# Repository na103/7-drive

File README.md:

# 7-drive
7-drive is a remake of an Amiga accessory made by the company Logica in Italy, it is installed on the external drive port and can show, in the 7-segment display, the activity of the df0 or df1 drive.
<br>
it's not particularly useful, maybe it was in the past when you spent your time copying hundreds of floppies.<br>
however it seems nice to me as an object to add to our amiga.
<br><br>

<br>
you can see 7-drive in action in this [short video](https://youtu.be/NdRC49Pznj0)
<br><br>

## Bill of materials
| Qt. |    Description     |             Designator          |    Mouser  Part    |             Note              |
|:---:|--------------------|---------------------------------|--------------------|-------------------------------|
|1    |74LS27              | U2                              |SN74LS27N           |                               |
|1    |74LS00              | U3                              |SN74LS00N           |                               |
|2    |Decade up-down counter| U4 U5                         |CD40110BE           |                               |
|2    |7 segment display   | DS1 DS2                         |TDSO3160-L          |                               |
|2    |Diode 1N4148        | D1 D2                           |1N4148              |                               |
|1    |Resistor 3.9K       | R1                              |MFR25SFTE26-3K9     |                               |
|4    |Resistor net. 220R  | RN1 - RN4                       |4608X-102-221LF     |                               |
|1    |Capacitor 4.7 nF    | C1                              |K472J20C0GF5TH5     |                               |
|2    |Capacitor 100 nF    | C2 C3                           |K104K15X7RF5TH5     |                               |
|1    |Switch 2P3T         | SW1                             |EG1201A             |                               |
|1    |Db23 male           | J1                              |                    |    on ebay or [amigatore.eu](https://amigastore.eu/en/790-db23-male-connector.html)    |
|1    |Db23 female         | J2                              |                    |    on ebay or [amigastore.eu](https://amigastore.eu/en/810-db23-female-connector.html)   |
|1    |15-Pin female header| J3                              |15Fx1-254mm         |                               |
|1    |18-Pin male header  | J5                              |22-28-4183          |                               |
|1    |15-Pin male header  | J6                              |22-28-8152          |                               |

here you can find the mouser project with all the components, Db23 connectors excluded.
[https://www.mouser.com/ProjectManager/ProjectDetail.aspx?AccessID=75b1d9bf4b](https://www.mouser.com/ProjectManager/ProjectDetail.aspx?AccessID=75b1d9bf4b)

## Building notes

* you can see [here](https://github.com/na103/7-drive/tree/main/img) the steps to follow to build the board.
* gerber of the three board is inside kicad projects
* switch in upper position show DF0 activity, down DF1
* is avaible an optional 3d printed case. thanks to Roberto Camparini for stl file

<br>
If you found this my work useful, please consider buying me a cup of coffee if you want:<br>

# License

This work is licensed under a Creative Commons Attribution 4.0 International License. See [https://creativecommons.org/licenses/by/4.0/](https://creativecommons.org/licenses/by/4.0/).

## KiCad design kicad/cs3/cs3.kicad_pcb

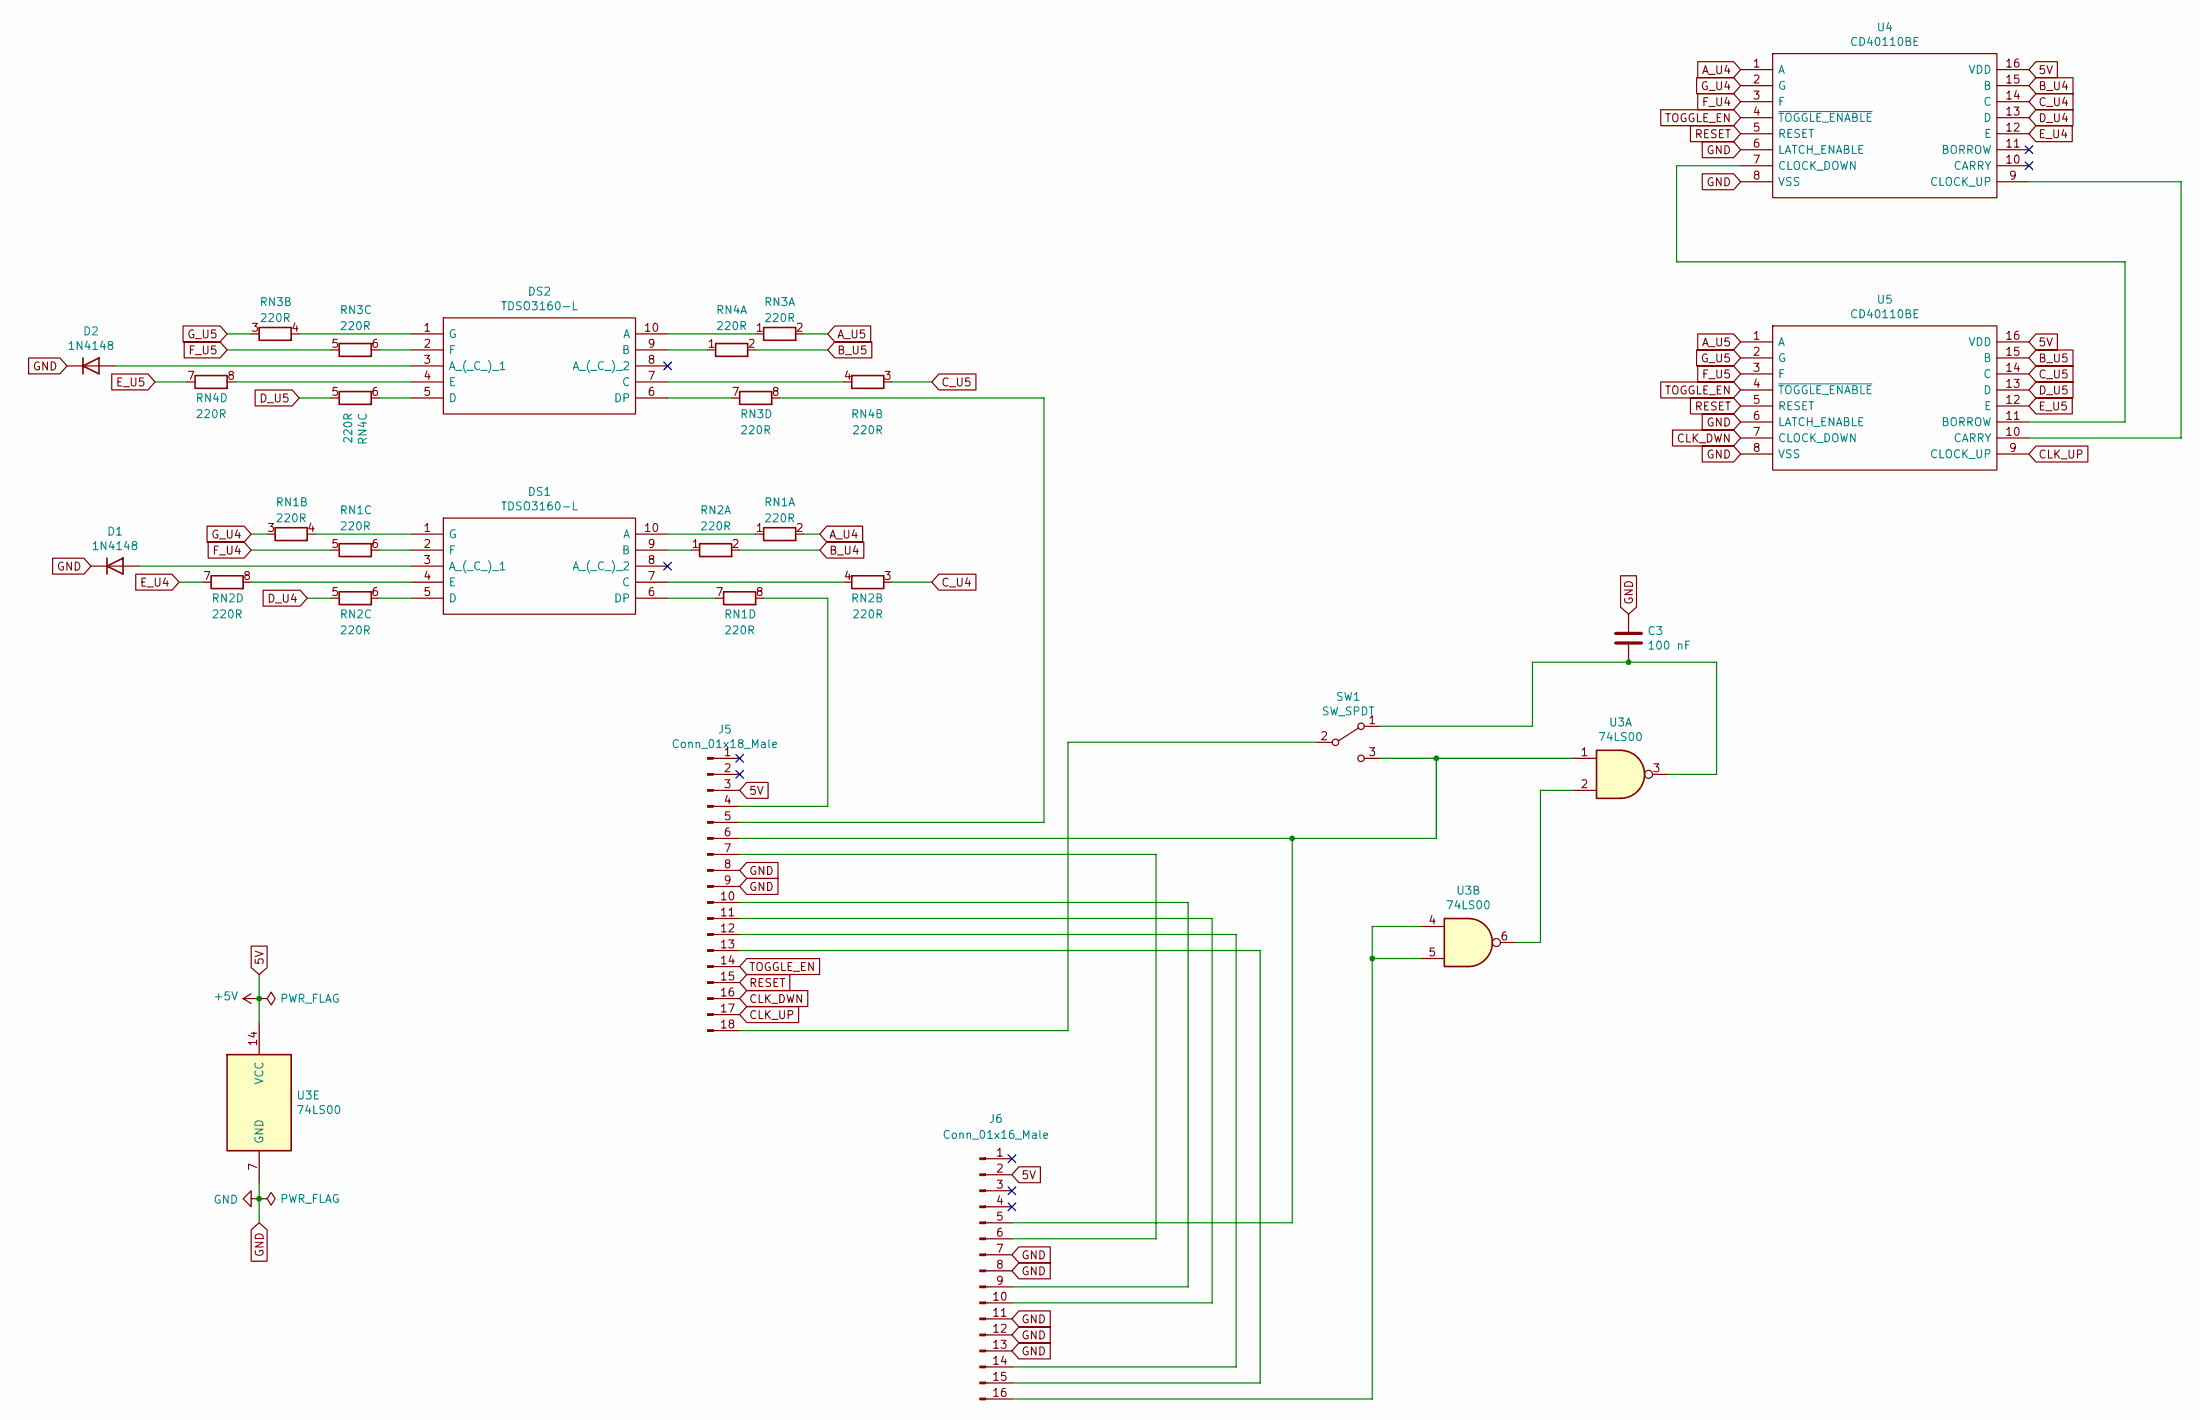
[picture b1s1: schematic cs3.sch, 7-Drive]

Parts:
C3: 100 nF; C_Disc_D6.0mm_W2.5mm_P5.00mm
D1, D2: 1N4148; D_A-405_P7.62mm_Horizontal
DS1, DS2: TDSO3160-L; TDSO3160L; Manufacturer_Part_Number TDSO3160-L; Mouser Part Number 78-TDSO3160-L
J5: Conn_01x18_Male; PinHeader_1x18_P2.54mm_Vertical
J6: Conn_01x16_Male; PinHeader_1x16_P2.54mm_Horizontal
RN1, RN2, RN3, RN4: 220R; R_Array_SIP8
SW1: SW_SPDT; SW_Slide_1P2T_SPDT
U3: 74LS00; DIP-14_W7.62mm
U4, U5: CD40110BE; DIP794W53P254L1930H508Q16N; Manufacturer_Part_Number CD40110BE; Mouser Part Number 595-CD40110BE

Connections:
5V: J5.3, J6.2, U3.14 (VCC), U4.16 (VDD), U5.16 (VDD)
A_U4: RN1.2 (R1.2), U4.1 (A)
A_U5: RN3.2 (R1.2), U5.1 (A)
B_U4: RN2.2 (R1.2), U4.15 (B)
B_U5: RN4.2 (R1.2), U5.15 (B)
CLK_DWN: J5.16, U5.7 (CLOCK_DOWN)
CLK_UP: J5.17, U5.9 (CLOCK_UP)
C_U4: RN2.3 (R2.1), U4.14 (C)
C_U5: RN4.3 (R2.1), U5.14 (C)
D_U4: RN2.5 (R3.1), U4.13 (D)
D_U5: RN4.5 (R3.1), U5.13 (D)
E_U4: RN2.7 (R4.1), U4.12 (E)
E_U5: RN4.7 (R4.1), U5.12 (E)
F_U4: RN1.5 (R3.1), U4.3 (F)
F_U5: RN3.5 (R3.1), U5.3 (F)
GND: C3.1, D1.1 (K), D2.1 (K), J5.8, J5.9, J6.7, J6.8, J6.11, J6.12, J6.13, U3.7 (GND), U4.6 (LATCH_ENABLE), U4.8 (VSS), U5.6 (LATCH_ENABLE), U5.8 (VSS)
G_U4: RN1.3 (R2.1), U4.2 (G)
G_U5: RN3.3 (R2.1), U5.2 (G)
unnamed: C3.2, SW1.1 (A), U3.3
unnamed: D1.2 (A), DS1.3 (A_(_C_)_1)
unnamed: D2.2 (A), DS2.3 (A_(_C_)_1)
unnamed: DS1.1 (G), RN1.4 (R2.2)
unnamed: DS1.2 (F), RN1.6 (R3.2)
unnamed: DS1.4 (E), RN2.8 (R4.2)
unnamed: DS1.5 (D), RN2.6 (R3.2)
unnamed: DS1.6 (DP), RN1.7 (R4.1)
unnamed: DS1.7 (C), RN2.4 (R2.2)
unnamed: DS1.9 (B), RN2.1 (R1.1)
unnamed: DS1.10 (A), RN1.1 (R1.1)
unnamed: DS2.1 (G), RN3.4 (R2.2)
unnamed: DS2.2 (F), RN3.6 (R3.2)
unnamed: DS2.4 (E), RN4.8 (R4.2)
unnamed: DS2.5 (D), RN4.6 (R3.2)
unnamed: DS2.6 (DP), RN3.7 (R4.1)
unnamed: DS2.7 (C), RN4.4 (R2.2)
unnamed: DS2.9 (B), RN4.1 (R1.1)
unnamed: DS2.10 (A), RN3.1 (R1.1)
unnamed: J5.4, RN1.8 (R4.2)
unnamed: J5.5, RN3.8 (R4.2)
unnamed: J5.6, J6.5, SW1.3 (C), U3.1
unnamed: J5.7, J6.6
unnamed: J5.10, J6.9
unnamed: J5.11, J6.10
unnamed: J5.12, J6.14
unnamed: J5.13, J6.15
unnamed: J5.18, SW1.2 (B)
unnamed: J6.16, U3.4, U3.5
unnamed: U3.2, U3.6
unnamed: U4.7 (CLOCK_DOWN), U5.11 (BORROW)
unnamed: U4.9 (CLOCK_UP), U5.10 (CARRY)
RESET: J5.15, U4.5 (RESET), U5.5 (RESET)
TOGGLE_EN: J5.14, U4.4 (~TOGGLE_ENABLE), U5.4 (~TOGGLE_ENABLE)

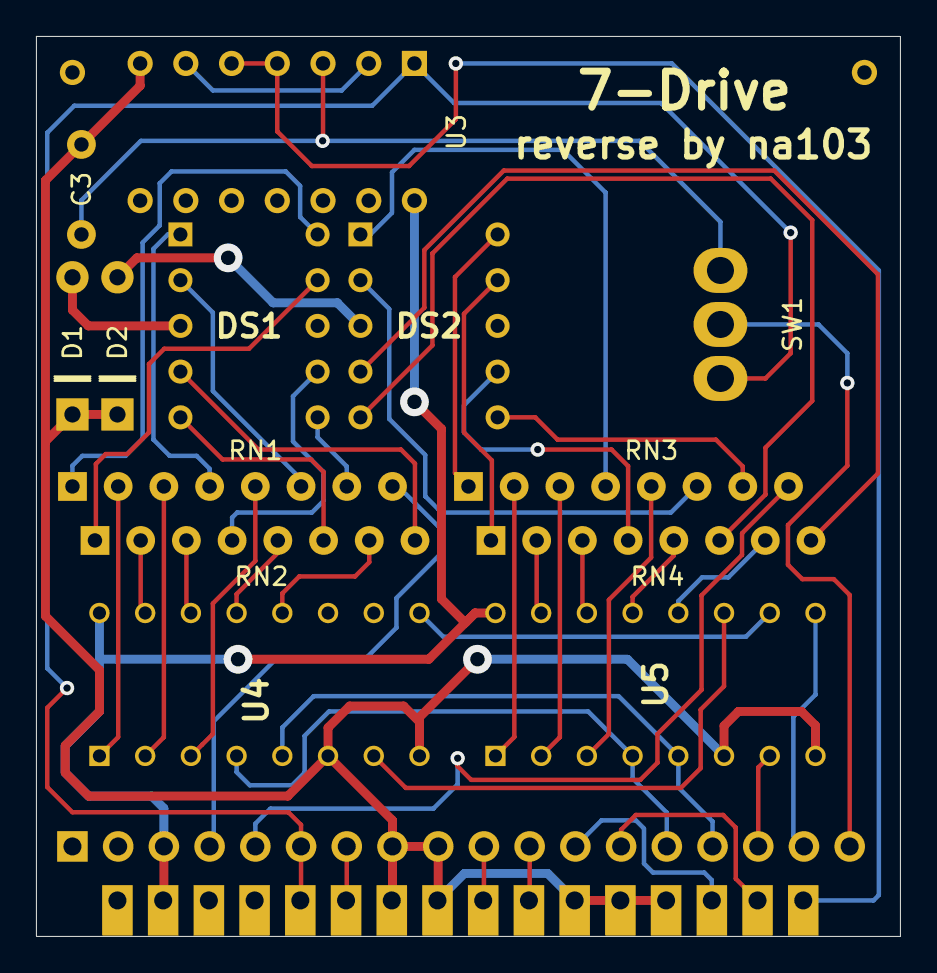
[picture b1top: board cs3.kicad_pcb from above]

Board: 2 copper layers, 48.0 x 50.0 mm, 15 parts (1 on the bottom side), 52 nets.

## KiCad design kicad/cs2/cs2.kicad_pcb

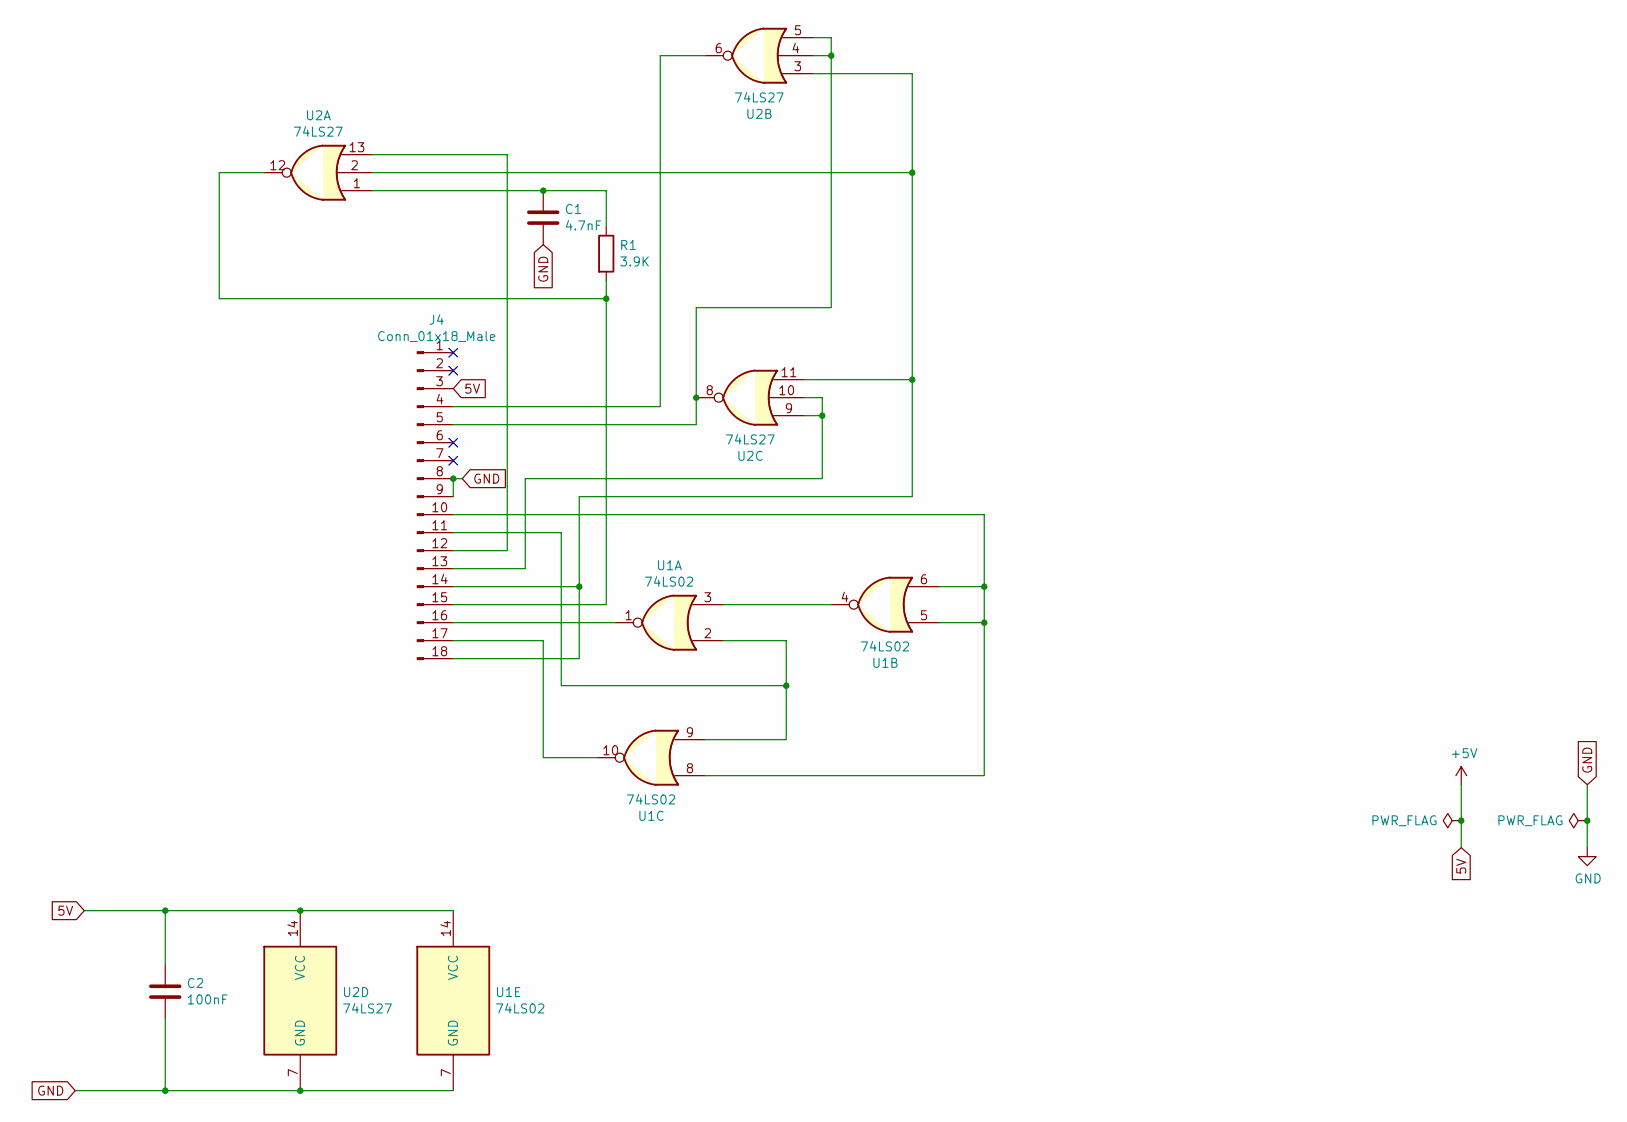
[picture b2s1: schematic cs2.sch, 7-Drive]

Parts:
C1: 4.7nF; C_Disc_D4.3mm_W1.9mm_P5.00mm
C2: 100nF; C_Disc_D4.3mm_W1.9mm_P5.00mm
J4: Conn_01x18_Male; PinHeader_1x18_P2.54mm_Vertical
R1: 3.9K; R_Axial_DIN0207_L6.3mm_D2.5mm_P10.16mm_Horizontal
U1: 74LS02; DIP-14_W7.62mm
U2: 74LS27; DIP-14_W7.62mm

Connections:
5V: C2.1, J4.3, U1.14 (VCC), U2.14 (VCC)
GND: C1.2, C2.2, J4.8, J4.9, U1.7 (GND), U2.7 (GND)
unnamed: C1.1, R1.1, U2.1
unnamed: J4.4, U2.6
unnamed: J4.5, U2.4, U2.5, U2.8
unnamed: J4.10, U1.5, U1.6, U1.8
unnamed: J4.11, U1.2, U1.9
unnamed: J4.12, U2.13
unnamed: J4.13, U2.9, U2.10
unnamed: J4.14, J4.18, U2.2, U2.3, U2.11
unnamed: J4.15, R1.2, U2.12
unnamed: J4.16, U1.1
unnamed: J4.17, U1.10
unnamed: U1.3, U1.4

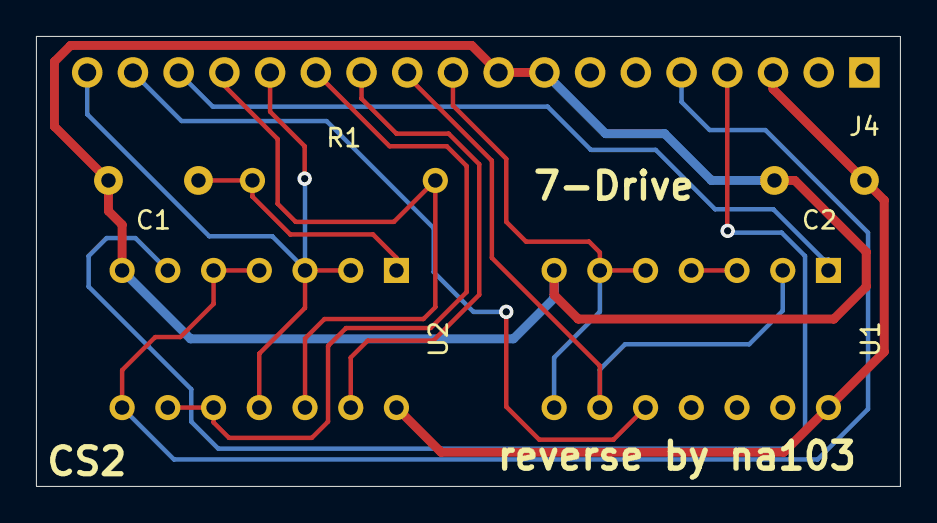
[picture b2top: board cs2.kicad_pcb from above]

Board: 2 copper layers, 48.0 x 25.0 mm, 6 parts (0 on the bottom side), 14 nets.

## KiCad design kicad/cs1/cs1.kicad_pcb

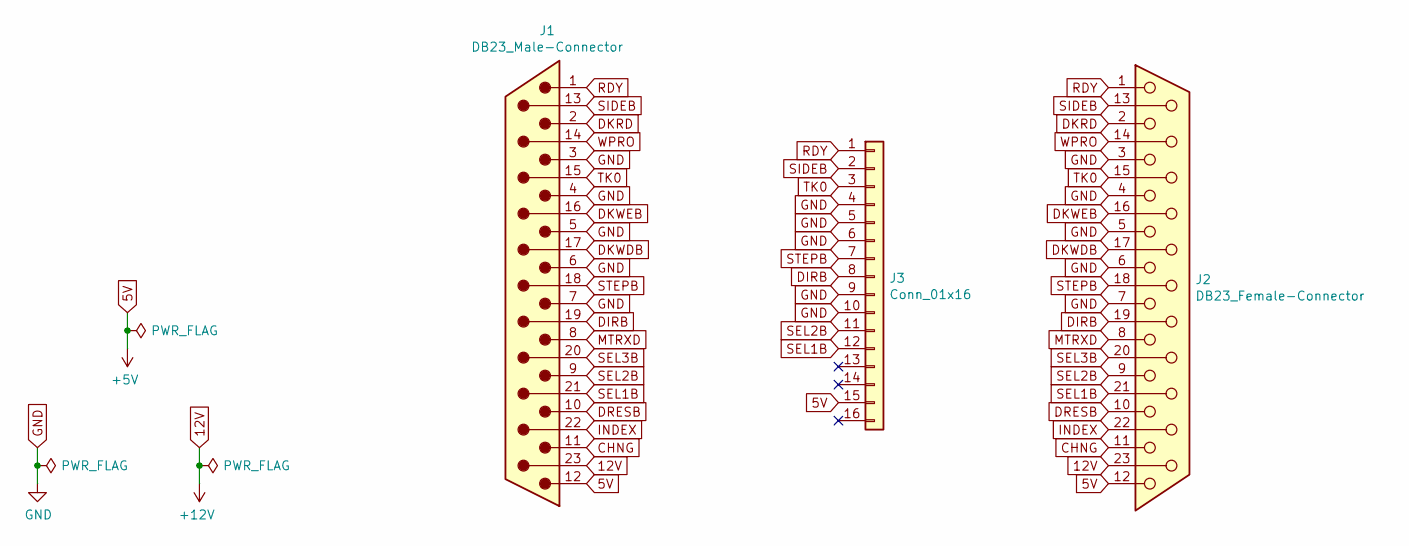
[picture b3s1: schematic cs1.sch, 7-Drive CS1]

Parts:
J1: DB23_Male-Connector; DSUB-23_Male_EdgeMount_P2.77mm
J2: DB23_Female-Connector; DSUB-23_Female_EdgeMount_P2.77mm
J3: Conn_01x16; PinHeader_1x16_P2.54mm_Vertical

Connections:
5V: J1.12, J2.12, J3.15
12V: J1.23, J2.23
CHNG: J1.11, J2.11
DIRB: J1.19, J2.19, J3.8
DKRD: J1.2, J2.2
DKWDB: J1.17, J2.17
DKWEB: J1.16, J2.16
DRESB: J1.10, J2.10
GND: J1.3, J1.4, J1.5, J1.6, J1.7, J2.3, J2.4, J2.5, J2.6, J2.7, J3.4, J3.5, J3.6, J3.9, J3.10
INDEX: J1.22, J2.22
MTRXD: J1.8, J2.8
RDY: J1.1, J2.1, J3.1
SEL1B: J1.21, J2.21, J3.12
SEL2B: J1.9, J2.9, J3.11
SEL3B: J1.20, J2.20
SIDEB: J1.13, J2.13, J3.2
STEPB: J1.18, J2.18, J3.7
TK0: J1.15, J2.15, J3.3
WPRO: J1.14, J2.14

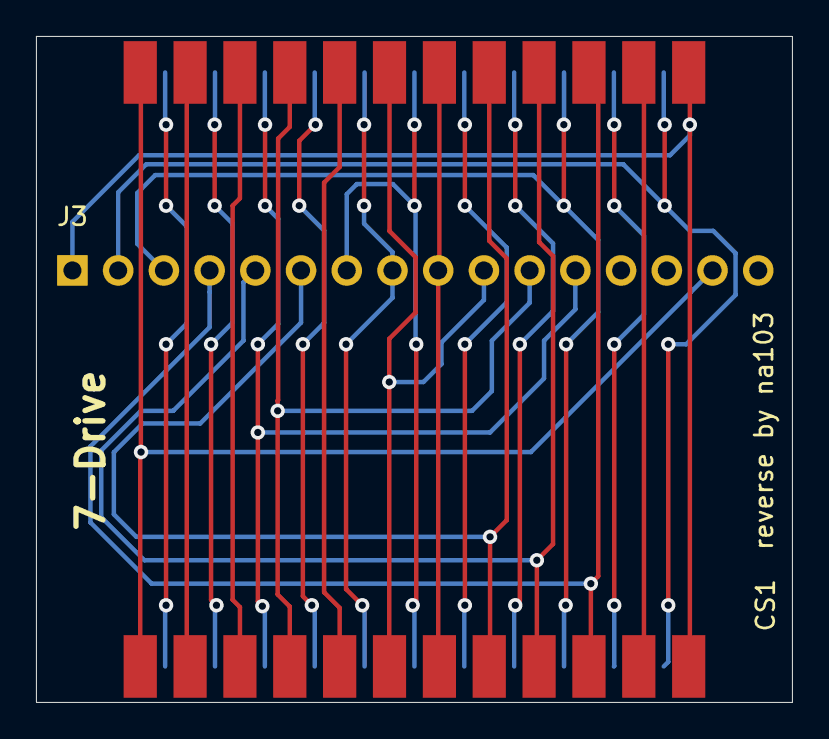
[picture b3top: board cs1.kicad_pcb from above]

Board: 2 copper layers, 42.0 x 37.0 mm, 3 parts (0 on the bottom side), 19 nets.

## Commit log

2023-07-02 Create LICENSE
2023-07-02 Kicad projects
2023-07-02 pictures construction steps
2023-07-03 case picture
